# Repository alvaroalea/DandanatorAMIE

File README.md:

# ZX Dandanator with Multiply Addon all in one
## Alea's Multiply Integrated Edition

UNDER LICENSE Creative Commons Attribution-NonCommercial-ShareAlike 4.0 International (CC BY-NC-SA 4.0)
- If you remix, transform, or build upon the material, you must distribute your contributions under the same license as the original.
- You may not use the material for commercial purposes.
- You must give appropriate credit, provide a link to the license, and indicate if changes were made. You may do so in any reasonable manner, but not in any way that suggests the licensor endorses you or your use.

Original Design by Dandare, mad3001 and OverClk

PCB Design of the V2.1AMIE edition by AlvaroAlea

This is a project to integrate in only one PCB (well, in three) the ZX Dandanator Cartridge for ZX Spectrum and the Multiply Addon.

Check the father projects:

http://www.dandare.es

https://github.com/mad3001/Multiply

Your can download the programs need for programing GAL & PIC on this links

## Features

* 512Kb of flash memory for zero seconds load of games with a fancy menu

* microSD Card Slot for load of snapshots (Z80 and SNA) and tape files, also to program the flash memory

* microUSB conection for transfer flash memory from PC to Dandanator

* A multi-protocol Joystick conector that provide a Kempston Interface and allow to use any atari, SJS, or megadrive joystick with any ZX Spectrum

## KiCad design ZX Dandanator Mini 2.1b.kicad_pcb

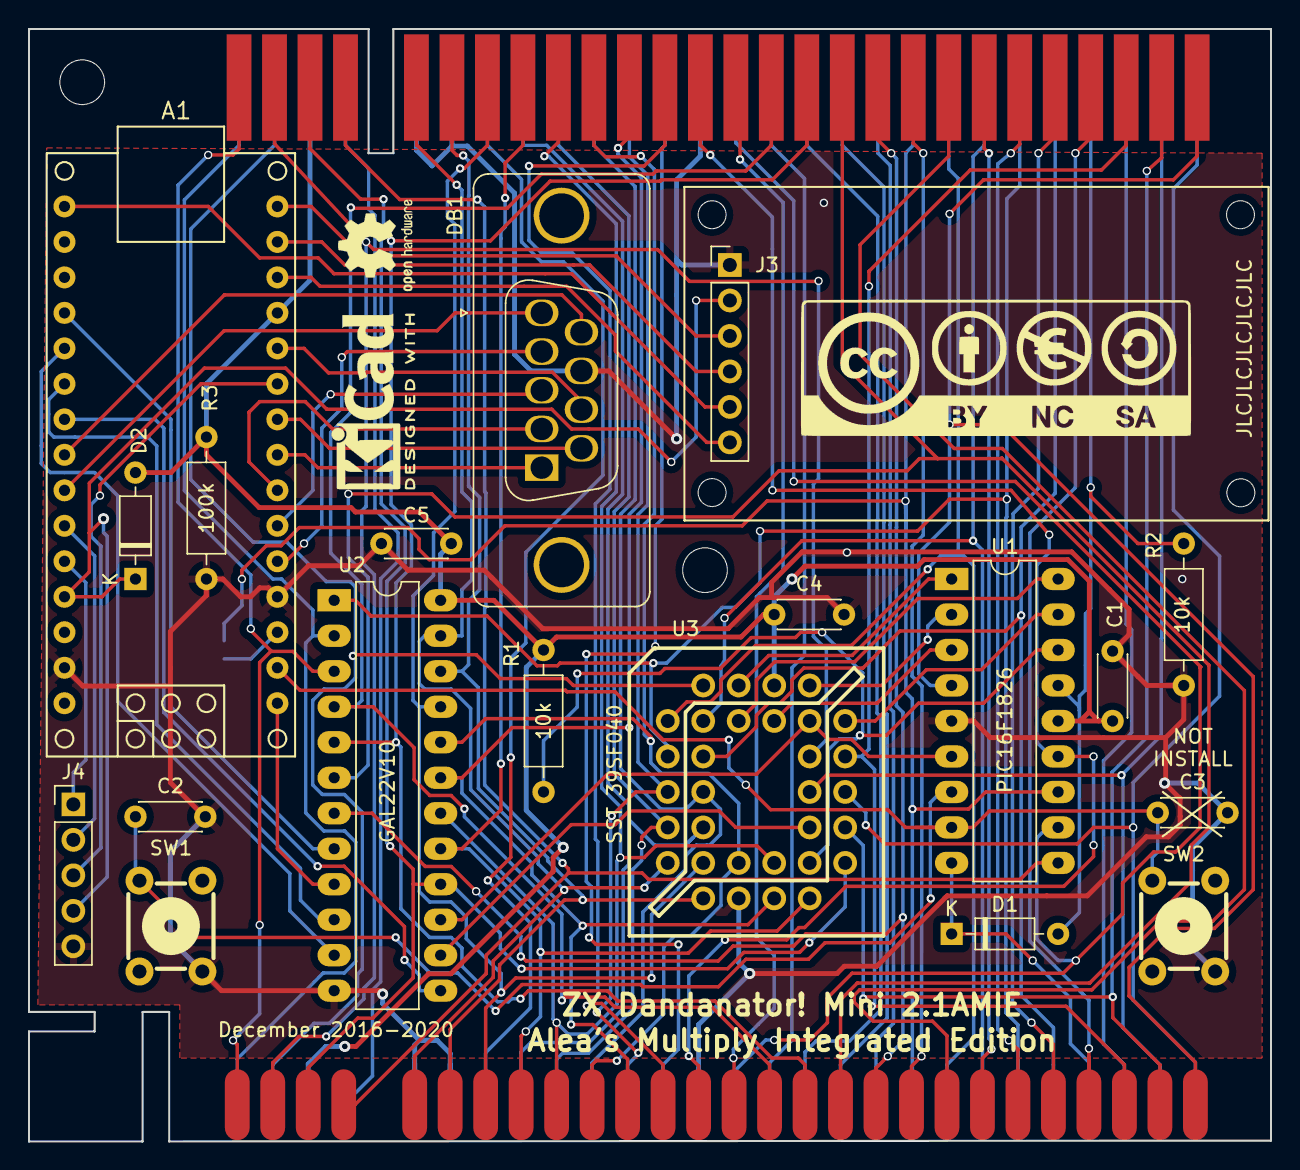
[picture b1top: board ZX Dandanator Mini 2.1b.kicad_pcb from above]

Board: 2 copper layers, 88.9 x 79.6 mm, 28 parts (1 on the bottom side), 85 nets.

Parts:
A1: Arduino_Nano; arduino_nano
C1, C2, C3, C4, C5: 100nf; C_Disc_D4.3mm_W1.9mm_P5.00mm
D1, D2: 1n4148; D_DO-35_SOD27_P7.62mm_Horizontal
DB1: Kempston Passthrough; DSUB-9_Female_Vertical_P2.77x2.84mm_MountingHoles
H1, H2: MountingHole; MountingHole_3.2mm_M3_ISO7380
H3, H4, H5, H6: MountingHole; MountingHole_2mm
J1: ZX_48K_EDGE; ZX_CONN
J2: ZX_48K_EDGE; ZX_BUS
J3: Conn_01x06; PinHeader_1x06_P2.54mm_Vertical
J4: Conn_01x05; PinHeader_1x05_P2.54mm_Vertical
JP1: Jumper_2_Open; SolderJumper-2_P1.3mm_Open_RoundedPad1.0x1.5mm
R1, R2: 10k; R_Axial_DIN0207_L6.3mm_D2.5mm_P10.16mm_Horizontal
R3: 100k; R_Axial_DIN0207_L6.3mm_D2.5mm_P10.16mm_Horizontal
SW1, SW2: SW_PUSH; PCB_PUSH
U1: PIC16F1826; DIP-18_W7.62mm_LongPads
U2: GAL22V10; DIP-24_W7.62mm_LongPads
U3: SST 39SF040; plcc32_pth-skt

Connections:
+5V: A1.12 (D9), C1.1, C4.1, C5.1, D2.2 (A), J1.A3 (+5), J2.A3 (+5), R1.1, R3.1, U1.14 (VDD), U2.24 (VCC), U3.32 (VCC)
+9V: J1.A4 (+9), J2.A4 (+9)
+12V: J1.B22 (+12), J2.B22 (+12)
-5V: J1.B20 (-5), J2.B20 (-5)
-12V: J1.B23 (-12), J2.B23 (-12)
A0: J1.A9 (A0), J2.A9 (A0), U3.12 (A0)
A1: J1.A10 (A1), J2.A10 (A1), U3.11 (A1)
A2: J1.A11 (A2), J2.A11 (A2), U3.10 (A2)
A3: J1.A12 (A3), J2.A12 (A3), U3.9 (A3)
A4: J1.A24 (A4), J2.A24 (A4), U3.8 (A4)
A5: J1.A23 (A5), J2.A23 (A5), U2.1 (A5), U3.7 (A5)
A6: J1.A22 (A6), J2.A22 (A6), U3.6 (A6)
A7: J1.A21 (A7), J2.A21 (A7), U3.5 (A7)
A8: J1.B26 (A8), J2.B26 (A8), U3.27 (A8)
A9: J1.A27 (A9), J2.A27 (A9), U3.26 (A9)
A10: J1.B27 (A10), J2.B27 (A10), U3.23 (A10)
A11: J1.A28 (A11), J2.A28 (A11), U3.25 (A11)
A12: J1.A2 (A12), J2.A2 (A12), U3.4 (A12)
A13: J1.B2 (A13), J2.B2 (A13), U3.28 (A13)
A14: J1.A1 (A14), J2.A1 (A14), U2.2 (A14)
A15: J1.B1 (A15), J2.B1 (A15), U2.3 (A15)
ArD7: A1.10 (D7), J4.3
BUSACK: J1.A26 (BUSACK), J2.A26 (BUSACK)
BUSREQ: J1.A19 (BUSRQ), J2.A19 (BUSRQ)
CLOCK: J1.A8 (CLOCK), J2.A8 (CLOCK)
CS: A1.13 (D10), J3.6
D0: J1.B6 (D0), J2.B6 (D0), U2.23 (D0), U3.13 (DQ0)
D1: J1.B7 (D1), J2.B7 (D1), U2.22 (D1), U3.14 (DQ1)
D2: J1.B8 (D2), J2.B8 (D2), U2.21 (D2), U3.15 (DQ2)
D3: J1.B11 (D3), J2.B11 (D3), U2.20 (D3), U3.17 (DQ3)
D4: J1.B12 (D4), J2.B12 (D4), U2.19 (D4), U3.18 (DQ4)
D5: J1.B10 (D5), J2.B10 (D5), U2.18 (D5), U3.19 (DQ5)
D6: J1.B9 (D6), J2.B9 (D6), U2.17 (D6), U3.20 (DQ6)
D7: J1.B3 (D7), J2.B3 (D7), U2.16 (D7), U3.21 (DQ7)
EP_CE: R1.2, U1.16 (RA7), U3.22 (CE#)
GND: A1.4 (GND), A1.29 (GND), C1.2, C2.2, C3.2, C4.2, C5.2, DB1.8, J1.A6 (GND), J1.A7 (GND), J1.A14 (GND), J2.A6 (GND), J2.A7 (GND), J2.A14 (GND), J3.1, J4.5, R2.2, R3.2, SW1.2, SW2.2, U1.5 (VSS), U2.12 (GND), U3.16 (VSS)
HALT: J1.B15 (HALT), J2.B15 (HALT)
INT: J1.B13 (INT), J2.B13 (INT)
IOREQ: J1.B17 (IOREQ), J2.B17 (IOREQ), U2.5 (/IOREQ)
IOREQGE: J1.A13 (IORQGE), J2.A13 (IORQGE)
J1-Up: A1.21 (AD2/D16), U2.10 (/J_Up)
J2-Down: A1.20 (AD1/D15), U2.11 (/J_Down)
J3-Left: A1.19 (AD0/D14), U2.8 (/J_Left)
J4-Right: A1.1 (D1/RX), U2.9 (/J_Right)
J6-Fire: A1.22 (AD3/D17), U2.13 (/J_Fire)
M1: J1.B24 (M1), J2.B24 (M1)
MISO: A1.15 (D12), J3.3
MOSI: A1.14 (D11), J3.4
MREQ: J1.B16 (MREQ), J2.B16 (MREQ), U2.4 (/MREQ)
Mul-RX: A1.2 (D0/TX), C3.1, SW2.1, U1.8 (RB2)
NMI: J1.B14 (NMI), J2.B14 (NMI), U1.13 (RB7)
unnamed: A1.3 (RESET), JP1.2 (B)
unnamed: A1.5 (D2), DB1.4
unnamed: A1.6 (D3), DB1.3
unnamed: A1.7 (D4), DB1.2
unnamed: A1.8 (D5), DB1.1
unnamed: A1.9 (D6), DB1.6
unnamed: A1.11 (D8), DB1.7
unnamed: A1.23 (AD4/D18), DB1.9
unnamed: A1.24 (AD5/D19), DB1.5
unnamed: A1.25 (AD6), J4.2
unnamed: A1.26 (AD7), J4.1
unnamed: A1.27 (5V), D2.1 (K), J3.2, J4.4
unnamed: C2.1, SW1.1, U1.7 (RB1)
OE1_128K: J1.B4, J2.B4, U1.10 (RB4)
PA14: U1.17 (RA0), U3.29 (A14)
PA15: U1.18 (RA1), U3.3 (A15)
PA16: U1.1 (RA2), U3.2 (A16)
PA17: U1.2 (RA3), U3.30 (A17)
PA18: U1.3 (RA4), U3.1 (A18)
PT_ROMCS: D1.2 (A), J2.A25 (ROMCS), R2.1, U1.15 (RA6)
RD: J1.B18 (RD), J2.B18 (RD), U2.6 (/RD)
RESET: J1.A20 (RESET), J2.A20 (RESET), JP1.1 (A), U1.12 (RB6)
RFSH: J1.B25 (RFSH), J2.B25 (RFSH)
ROMCS48K: D1.1 (K), J1.A25 (ROMCS), U1.9 (RB3)
Rom_RD: U2.14 (/Rom_RD), U3.24 (OE#)
Rom_WR: U1.6 (RB0), U2.15 (/Rom_WR), U3.31 (WE#)
SCK: A1.16 (D13), J3.5
TOP28: J1.B28, J2.B28, U1.4 (RA5/MCLR)
U: J1.A18 (U), J2.A18 (U)
V: J1.A17 (V), J2.A17 (V)
VIDEO/OE2_128K: J1.A15 (VIDEO), J2.A15 (VIDEO), U1.11 (RB5)
WAIT: J1.B21 (WAIT), J2.B21 (WAIT)
WR: J1.B19 (WR), J2.B19 (WR), U2.7 (/WR)
Y: J1.A16 (Y), J2.A16 (Y)

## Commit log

2020-11-24 initial
2020-11-25 upload project
2020-11-25 3d model
2020-11-26 small fix
2020-11-27 retoques
2020-11-28 logos

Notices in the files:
ZX Dandanator Mini 2.1b.kicad_pcb:
Distributed under Licence:
(C) 2016-2020
